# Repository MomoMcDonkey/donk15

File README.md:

# donk15
my hackclub stardance project!

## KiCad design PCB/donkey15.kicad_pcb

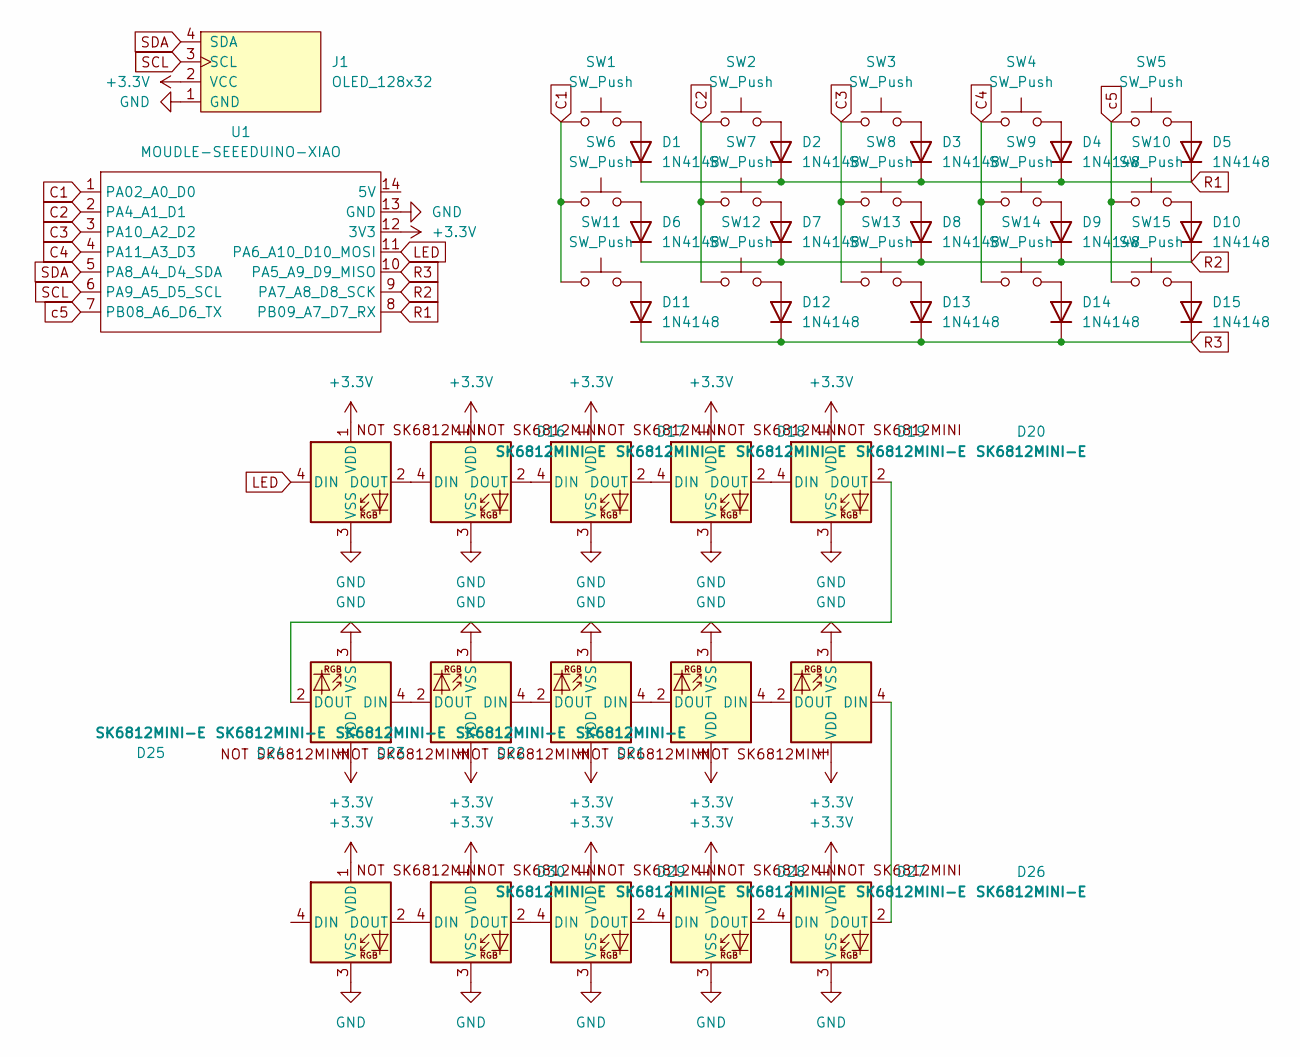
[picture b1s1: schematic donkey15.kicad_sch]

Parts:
D1, D2, D3, D4, D5, D6, D7, D8, D9, D10, D11, D12, D13, D14, D15: 1N4148; D_DO-35_SOD27_P7.62mm_Horizontal
D16, D17, D18, D19, D20, D21, D22, D23, D24, D25, D26, D27, D28, D29, D30: SK6812MINI-E; SK6812MINI-E (3d model)
J1: OLED_128x32; OLED_128x32 (3D MODEL)
SW1, SW2, SW3, SW4, SW5, SW6, SW7, SW8, SW9, SW10, SW11, SW12, SW13, SW14, SW15: SW_Push; CHERRY_MX_1U (3D MODEL)
U1: MOUDLE-SEEEDUINO-XIAO; XIAO-RP2040 (3D MODEL)

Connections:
+3.3V: D16.1 (VDD), D17.1 (VDD), D18.1 (VDD), D19.1 (VDD), D20.1 (VDD), D21.1 (VDD), D22.1 (VDD), D23.1 (VDD), D24.1 (VDD), D25.1 (VDD), D26.1 (VDD), D27.1 (VDD), D28.1 (VDD), D29.1 (VDD), D30.1 (VDD), J1.2 (VCC), U1.12 (3V3)
C1: SW1.1, SW6.1, SW11.1, U1.1 (PA02_A0_D0)
C2: SW2.1, SW7.1, SW12.1, U1.2 (PA4_A1_D1)
C3: SW3.1, SW8.1, SW13.1, U1.3 (PA10_A2_D2)
C4: SW4.1, SW9.1, SW14.1, U1.4 (PA11_A3_D3)
GND: D16.3 (VSS), D17.3 (VSS), D18.3 (VSS), D19.3 (VSS), D20.3 (VSS), D21.3 (VSS), D22.3 (VSS), D23.3 (VSS), D24.3 (VSS), D25.3 (VSS), D26.3 (VSS), D27.3 (VSS), D28.3 (VSS), D29.3 (VSS), D30.3 (VSS), J1.1 (GND), U1.13 (GND)
LED: D16.4 (DIN), U1.11 (PA6_A10_D10_MOSI)
unnamed: D1.2 (A), SW1.2
unnamed: D2.2 (A), SW2.2
unnamed: D3.2 (A), SW3.2
unnamed: D4.2 (A), SW4.2
unnamed: D5.2 (A), SW5.2
unnamed: D6.2 (A), SW6.2
unnamed: D7.2 (A), SW7.2
unnamed: D8.2 (A), SW8.2
unnamed: D9.2 (A), SW9.2
unnamed: D10.2 (A), SW10.2
unnamed: D11.2 (A), SW11.2
unnamed: D12.2 (A), SW12.2
unnamed: D13.2 (A), SW13.2
unnamed: D14.2 (A), SW14.2
unnamed: D15.2 (A), SW15.2
unnamed: D16.2 (DOUT), D17.4 (DIN)
unnamed: D17.2 (DOUT), D18.4 (DIN)
unnamed: D18.2 (DOUT), D19.4 (DIN)
unnamed: D19.2 (DOUT), D20.4 (DIN)
unnamed: D20.2 (DOUT), D25.2 (DOUT)
unnamed: D21.4 (DIN), D26.2 (DOUT)
unnamed: D21.2 (DOUT), D22.4 (DIN)
unnamed: D22.2 (DOUT), D23.4 (DIN)
unnamed: D23.2 (DOUT), D24.4 (DIN)
unnamed: D24.2 (DOUT), D25.4 (DIN)
unnamed: D26.4 (DIN), D27.2 (DOUT)
unnamed: D27.4 (DIN), D28.2 (DOUT)
unnamed: D28.4 (DIN), D29.2 (DOUT)
unnamed: D29.4 (DIN), D30.2 (DOUT)
R1: D1.1 (K), D2.1 (K), D3.1 (K), D4.1 (K), D5.1 (K), U1.8 (PB09_A7_D7_RX)
R2: D6.1 (K), D7.1 (K), D8.1 (K), D9.1 (K), D10.1 (K), U1.9 (PA7_A8_D8_SCK)
R3: D11.1 (K), D12.1 (K), D13.1 (K), D14.1 (K), D15.1 (K), U1.10 (PA5_A9_D9_MISO)
SCL: J1.3 (SCL), U1.6 (PA9_A5_D5_SCL)
SDA: J1.4 (SDA), U1.5 (PA8_A4_D4_SDA)
c5: SW5.1, SW10.1, SW15.1, U1.7 (PB08_A6_D6_TX)

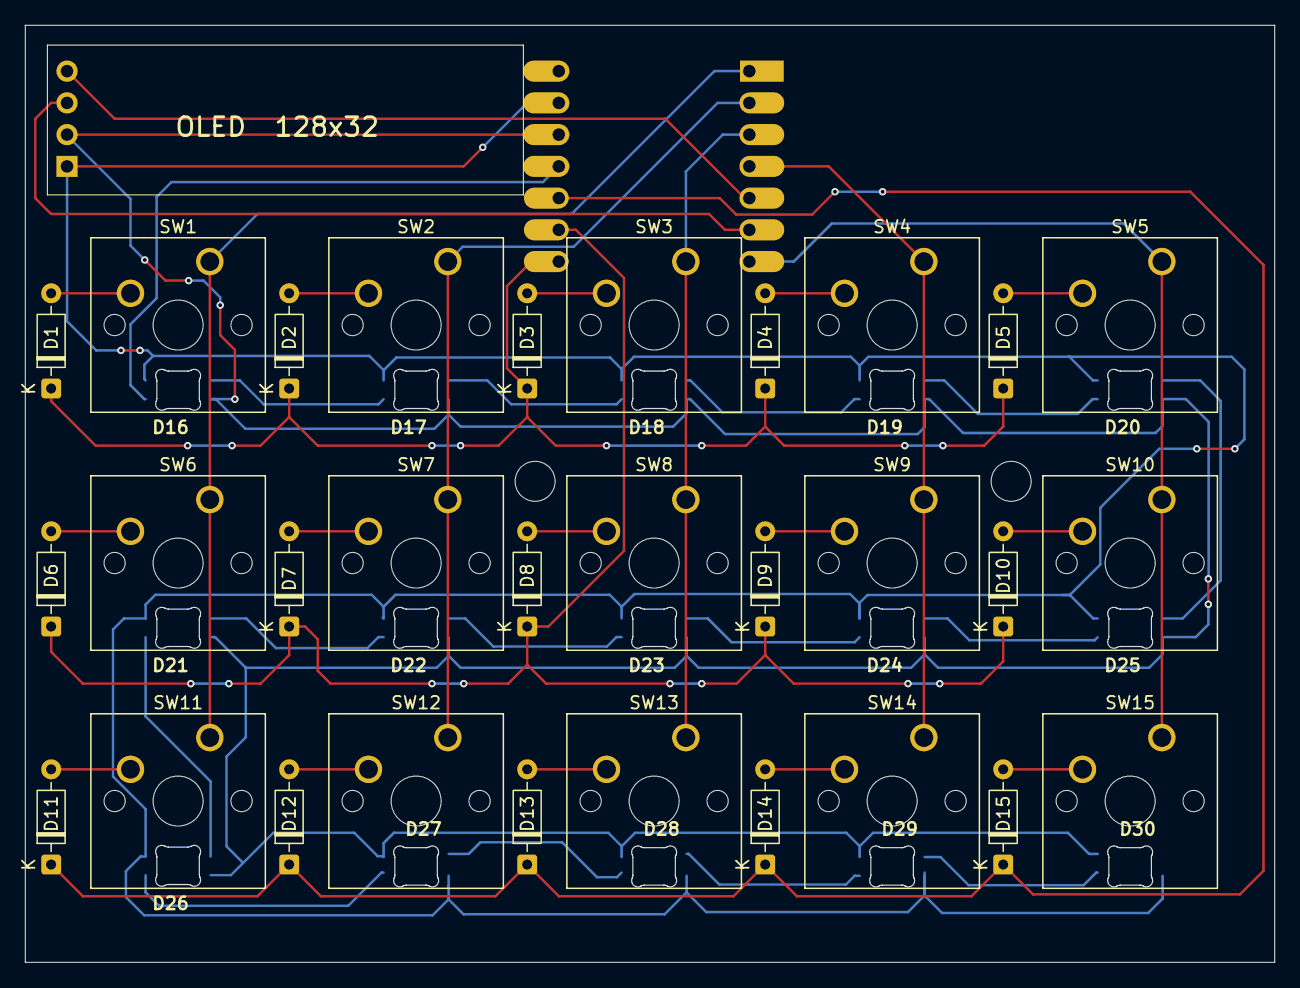
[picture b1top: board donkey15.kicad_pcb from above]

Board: 2 copper layers, 99.9 x 75.0 mm, 47 parts (1 on the bottom side), 42 nets.

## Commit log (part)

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2026-06-04 Add project title and description to README
